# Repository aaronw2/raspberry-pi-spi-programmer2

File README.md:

SOIC-8 and SOIC-16 SPI Flash Programming Hat for Raspberry PI

This hat allows the Raspberry PI to program both SOIC-8 and SOIC-16 SPI
NOR devices at 1.8 and 3.3 volts.  All features of this programmer can
be controlled via software.

While the current version of the board has switches and jumpers present,
a future version of this board will no longer require them since everything
can be controlled by GPIO pins.

SW1: This switch will enable and disable the programmer.  When disabled,
the power and signals to the sockets will be disabled and SPI NOR chips
may be safely installed or removed.  Software is able to read this switch
and a future software version will be able to override the switch.

SW2: This sets the voltage to use for powering and programming the SPI NOR
chips.  Software can read the position of this switch and a future version
of the software will be able to both read and override the switch setting.

JP1: This jumper should be installed if the board this hat is plugged into
does not support SPI chip select 1.  For example, the Rock64Pro board does
not provide CS1.  Software can read whether this jumper is installed or not
and can override the jumper.  A future version of the software will not
need the jumper since it will detect what type of board it is running on.

The SOIC-16 socket will only run in single lane mode.  Lanes 1, 2 and 3
are not supported by the Raspberry PI.

LEDs:
This board has 6 LEDs.

Power: D6: The white LED in the upper left will be lit when 5V is present.
Enabled: D1: This red LED will be lit when power is enabled to the sockets.
3.3V: D2: This LED will be lit when the board is configured for 3.3V
1.8V: D3: This LED will be lit when the board is configured for 1.8V
CS0: D4: This LED will light when there is activity with SPI CS0.
CS1: D5: This LED will light when there is activity with SPI CS1.

GPIOs used:
BMC17: Pin 13: This pin can be input or output.  If high, then 3.3 volts is
               selected, otherwise 1.8v is selected.  If not driven, then
               switch SW2 will control the signal.
BCM22: Pin 15: This pin is used to disable power and tri-state the outputs
               to the sockets.  This pin can be read, in which case SW1 will
               control the signal, or it may be driven to override the switch.
BCM5: Pin 29:  This pin is used to control whether CS1 is driven by CS0 or not.
               This pin can be read in which case the state can be controlled
               by JP1, or it can be driven to override the jumper.  This is
               needed if the board the hat is plugged in to does not support
               SPI CS1 such as the Rock64Pro board.

SPI pins:
BCM10: Pin 19: SPI MOSI signal
BCM9: Pin 21: SPI MISO signal
BCM11: Pin 23: SPI SCLK
BCM8: Pin 24: SPI CS0
BCM7: Pin 26: SPI CS1

I2C Pins:
BMCM0: Pin 27: EEPROM I2C SDA
BMC1: Pin 28: EEPROM I2C SCL

Power: This board draws power from 5V and 3.3V for internal logic.  The
       sockets power and socket I/O is controlled by a built-in regulator
       that uses the 5V supply to generate either 1.8 or 3.3V.

All parts can be found at https://digikey.com

=========== Using ==============

Do not install SPI NOR flash devices in both sockets at the same time.  A
future version of this board may support devices in both sockets.

1. Make sure that the board is in the disabled state
2. Select the proper voltage for the devices
3. Install a SOIC-8 and/or SOIC-16 SPI NOR device into the appropriate socket.
   Note: If not using a Raspberry PI do not install devices in both
         sockets.
4. Run the software to program the device(s)
5. Wait until programming is finished and make sure the enabled LED is not
   lit.  Set the switch to the disabled position.
6. Remove the SPI device

Software: TBD
Todo: Get the board back and assemble and test it then work on software.

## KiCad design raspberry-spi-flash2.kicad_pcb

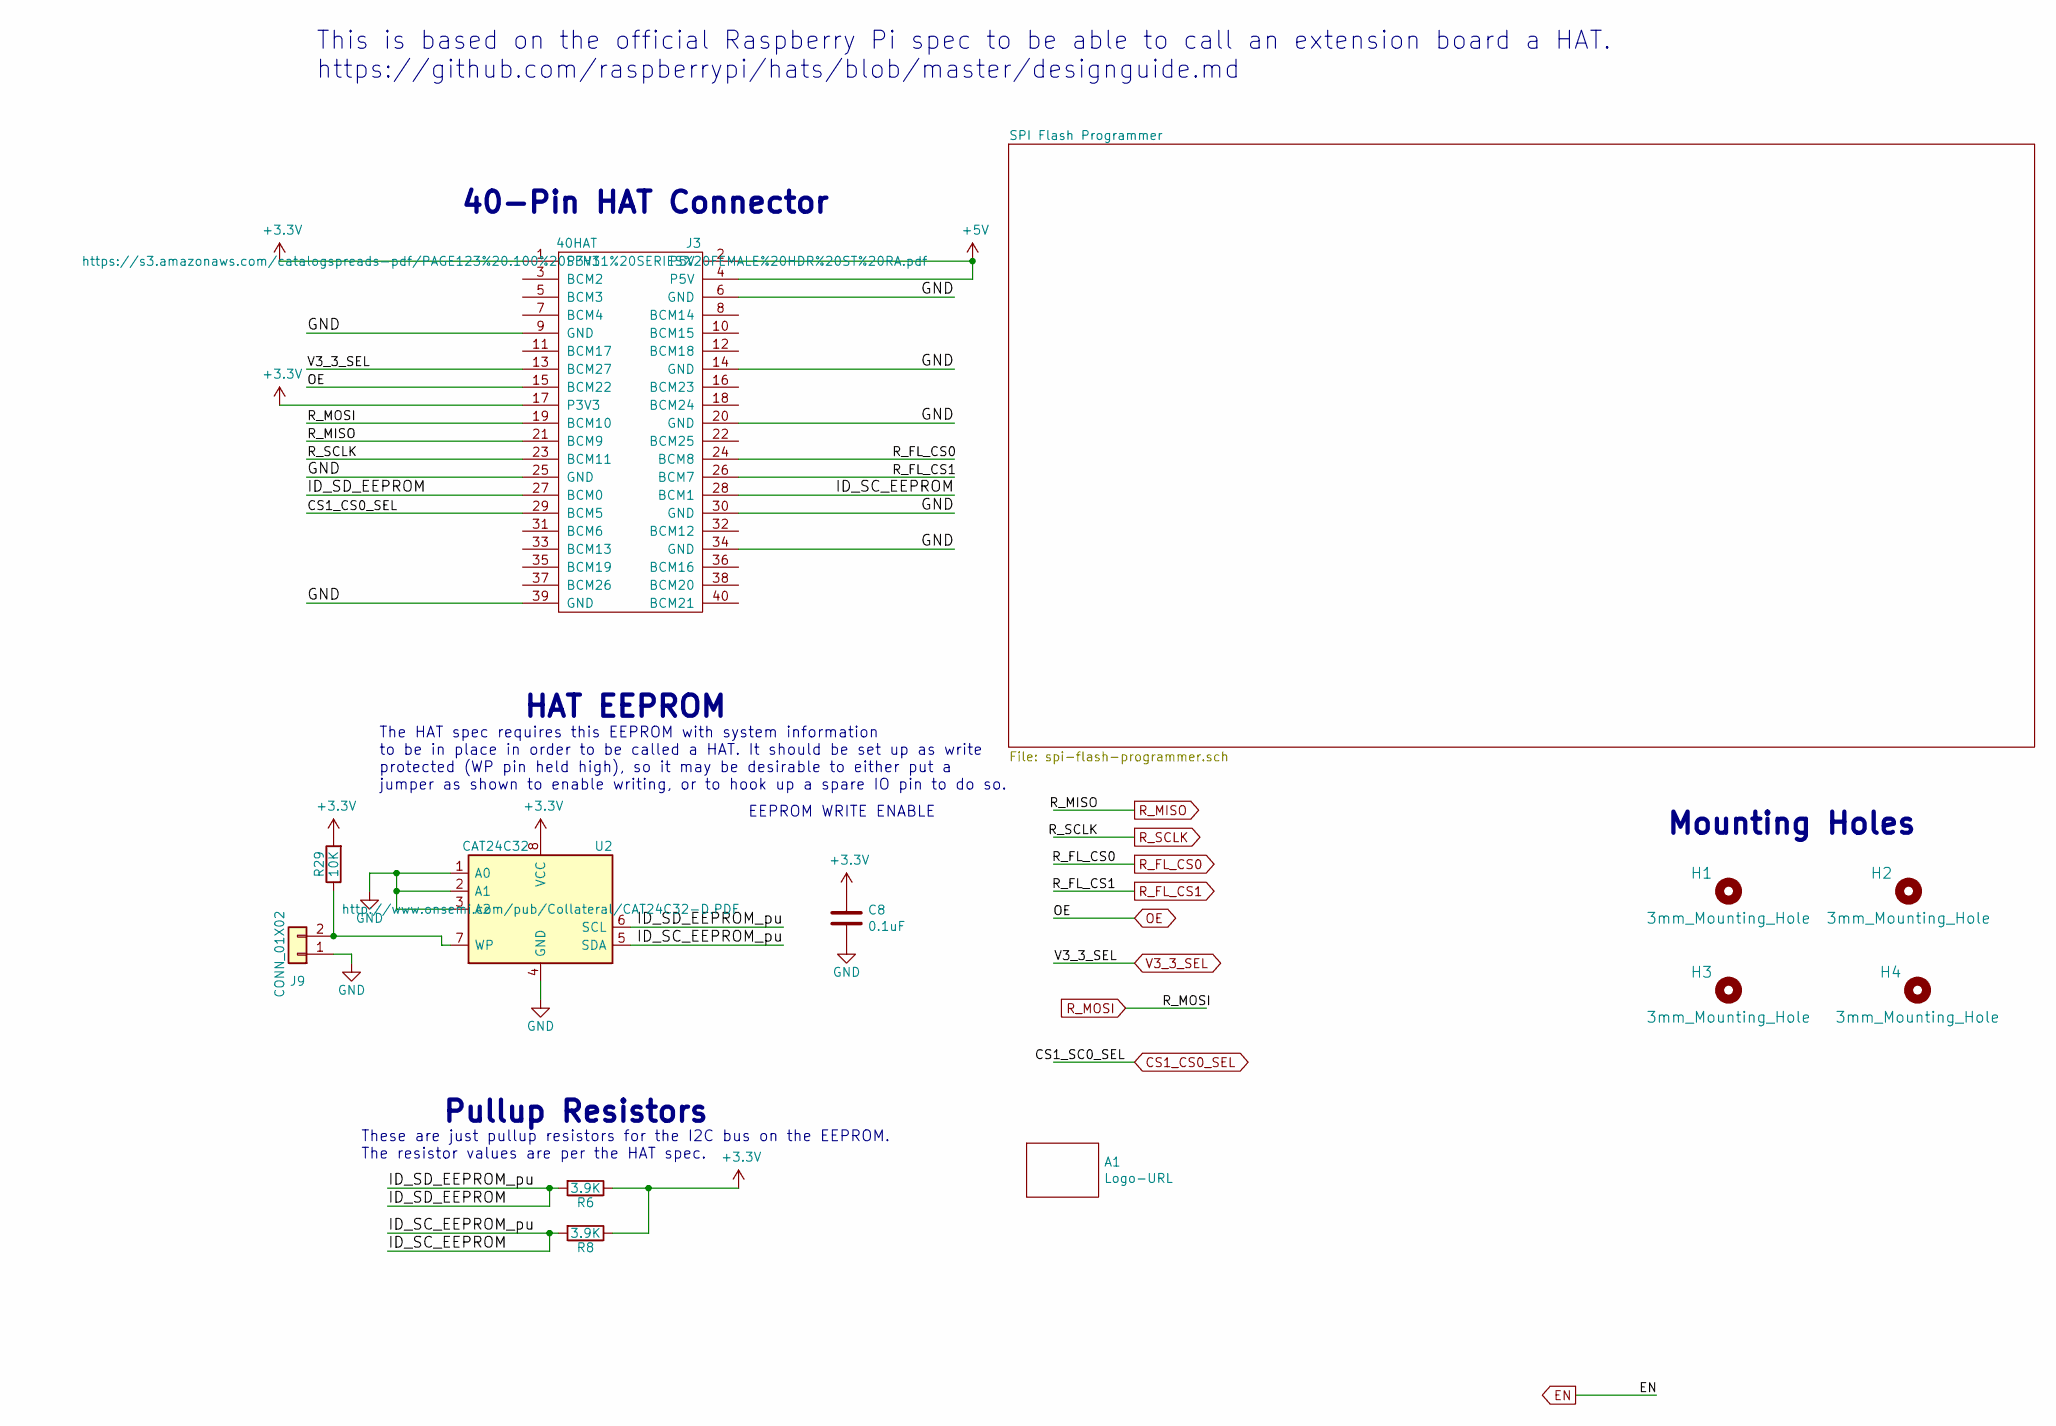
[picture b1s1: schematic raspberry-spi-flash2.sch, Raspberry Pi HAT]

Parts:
A1: Logo-URL; LOGO-raspberry-pi-spi-programmer2
C8: 0.1uF; C_0603_1608Metric
H1, H2, H3, H4: 3mm_Mounting_Hole; NPTH_3mm_ID
J3: 40HAT; PinSocket_2x20_P2.54mm_Vertical; MPN SFH11-PBPC-D20-ST-BK
J9: CONN_01X02; PinHeader_1x02_P2.54mm_Vertical
R6: 3.9K; R_0603_1608Metric; MPN RC0603FR-073K9L
R8: 3.9K; R_0603_1608Metric
R29: 10K; R_0603_1608Metric
U2: CAT24C32; SOIC-8_3.9x4.9mm_P1.27mm; MPN CAT24C32WI-GT3

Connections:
+3V3: C8.1, J3.1 (P3V3), J3.17 (P3V3), R6.1, R8.1, R29.2, U2.8 (VCC); also elsewhere on the board
+5V: J3.2 (P5V), J3.4 (P5V); also elsewhere on the board
/ID_SC_EEPROM: J3.28 (BCM1), R8.2, U2.5 (SDA)
/ID_SD_EEPROM: J3.27 (BCM0), R6.2, U2.6 (SCL)
CS1_CS0_SEL: J3.29 (BCM5); also elsewhere on the board
GND: C8.2, J3.6 (GND), J3.9 (GND), J3.14 (GND), J3.20 (GND), J3.25 (GND), J3.30 (GND), J3.34 (GND), J3.39 (GND), J9.1, U2.1 (A0), U2.2 (A1), U2.3 (A2), U2.4 (GND); also elsewhere on the board
unnamed: J9.2, R29.1, U2.7 (WP)
OE: J3.15 (BCM22); also elsewhere on the board
R_FL_CS0: J3.24 (BCM8); also elsewhere on the board
R_FL_CS1: J3.26 (BCM7); also elsewhere on the board
R_MISO: J3.21 (BCM9); also elsewhere on the board
R_MOSI: J3.19 (BCM10); also elsewhere on the board
R_SCLK: J3.23 (BCM11); also elsewhere on the board
V3_3_SEL: J3.13 (BCM27); also elsewhere on the board

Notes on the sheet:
EEPROM WRITE ENABLE
Pullup Resistors
HAT EEPROM
Mounting Holes
40-Pin HAT Connector
The HAT spec requires this EEPROM with system information to be in place in order to be called a HAT. It should be set up as write protected (WP pin held high), so it may be desirable to either put a jumper as shown to enable writing, or to hook up a spare IO pin to do so.
These are just pullup resistors for the I2C bus on the EEPROM. The resistor values are per the HAT spec.
This is based on the official Raspberry Pi spec to be able to call an extension board a HAT. https://github.com/raspberrypi/hats/blob/master/designguide.md

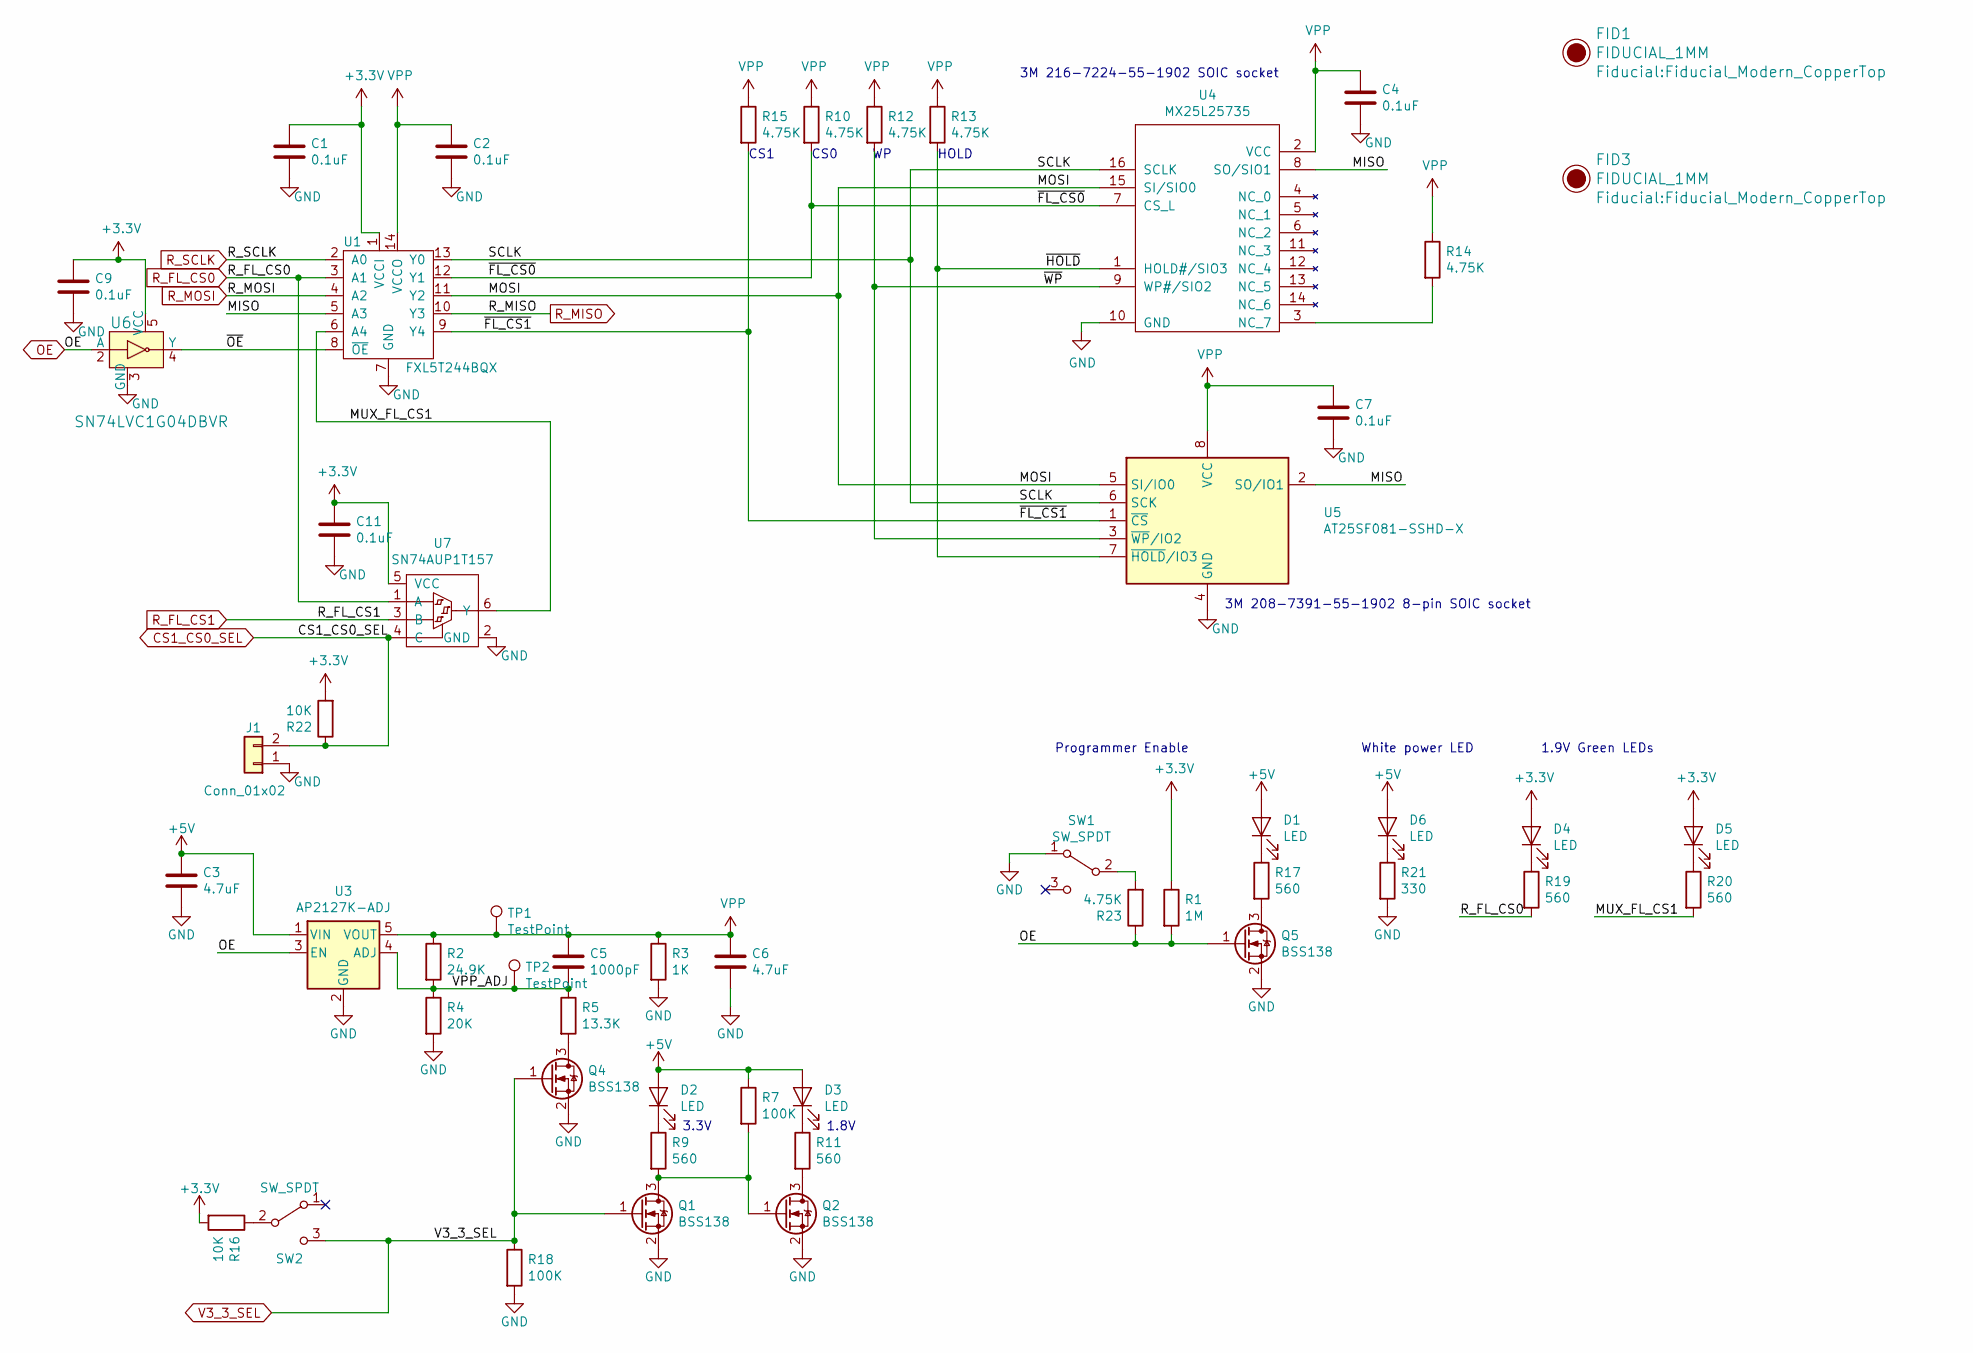
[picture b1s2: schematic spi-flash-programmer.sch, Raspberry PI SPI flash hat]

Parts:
C1, C2, C4, C7, C9, C11: 0.1uF; C_0603_1608Metric
C3, C6: 4.7uF; C_0603_1608Metric
C5: 1000pF; C_0603_1608Metric; MPN GRM188R61E475KE15D
D1, D2, D3: LED; LED_0603_1608Metric
D4, D5, D6: LED; LED_0603_1608Metric; MPN 5990060007F
FID1, FID3: FIDUCIAL_1MM; Fiducial_Modern_CopperTop
J1: Conn_01x02; PinHeader_1x02_P2.54mm_Vertical
Q1, Q2, Q4: BSS138; SOT-23
Q5: BSS138; SOT-23; MPN BSS138K
R1: 1M; R_0603_1608Metric
R2: 24.9K; R_0603_1608Metric; MPN RT0603DRE0724K3L
R3: 1K; R_0603_1608Metric
R4: 20K; R_0603_1608Metric; MPN RT0603FRE0720KL
R5: 13.3K; R_0603_1608Metric; MPN CRCW060313K3FKEA
R7, R18: 100K; R_0603_1608Metric
R9, R11, R17, R19, R20: 560; R_0603_1608Metric
R10, R12, R13, R14, R15, R23: 4.75K; R_0603_1608Metric
R16, R22: 10K; R_0603_1608Metric
R21: 330; R_0603_1608Metric
SW1, SW2: SW_SPDT; SW_STDP_CF-LD-1DC; MPN CF-LD-1DC-AW2W
TP1, TP2: TestPoint; TestPoint_THTPad_1.0x1.0mm_Drill0.5mm
U1: FXL5T244BQX; DQFN-14-1EP_2.5x3mm_EP2.2x1.7mm_Thermal
U3: AP2127K-ADJ; SOT-23-5
U4: MX25L25735; 216-7224-55-1902; MPN 216-7383-55-1902
U5: AT25SF081-SSHD-X; 208-7391-55-1902; MPN 208-7391-55-1902
U6: SN74LVC1G04DBVR; SOT-753; MPN SN74LVC1G04DBVR; Digi-Key_PN 296-11599-1-ND
U7: SN74AUP1T157; SOT-23-6; MPN SN74AUP1T157DCKR

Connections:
+3V3: C1.1, C9.1, C11.1, D4.2 (A), D5.2 (A), R1.1, R16.2, R22.2, U1.1 (VCCI), U6.5 (VCC), U7.5 (VCC); also elsewhere on the board
+5V: C3.1, D1.2 (A), D2.2 (A), D3.2 (A), D6.2 (A), R7.1, U3.1 (VIN); also elsewhere on the board
/SPI Flash Programmer/MISO: U1.5 (A3), U4.8 (SO/SIO1), U5.2 (SO/IO1)
/SPI Flash Programmer/MOSI: U1.11 (Y2), U4.15 (SI/SIO0), U5.5 (SI/IO0)
/SPI Flash Programmer/MUX_FL_CS1: R20.2, U1.6 (A4), U7.6 (Y)
/SPI Flash Programmer/SCLK: U1.13 (Y0), U4.16 (SCLK), U5.6 (SCK)
/SPI Flash Programmer/VPP_ADJ: C5.2, R2.2, R4.1, R5.1, TP2.1, U3.4 (ADJ)
/SPI Flash Programmer/~FL_CS0: R10.2, U1.12 (Y1), U4.7 (CS_L)
/SPI Flash Programmer/~FL_CS1: R15.2, U1.9 (Y4), U5.1 (~CS)
/SPI Flash Programmer/~HOLD: R13.2, U4.1 (HOLD#/SIO3), U5.7 (~HOLD~/IO3)
/SPI Flash Programmer/~OE: U1.8 (~OE), U6.4 (Y)
/SPI Flash Programmer/~WP: R12.2, U4.9 (WP#/SIO2), U5.3 (~WP~/IO2)
CS1_CS0_SEL: J1.2, R22.1, U7.4 (C); also elsewhere on the board
GND: C1.2, C2.2, C3.2, C4.2, C6.2, C7.2, C9.2, C11.2, J1.1, Q1.2 (S), Q2.2 (S), Q4.2 (S), Q5.2 (S), R3.2, R4.2, R18.2, R21.2, SW1.1 (A), U1.7 (GND), U3.2 (GND), U4.10 (GND), U5.4 (GND), U6.3 (GND), U7.2 (GND); also elsewhere on the board
unnamed: D1.1 (K), R17.1
unnamed: D2.1 (K), R9.1
unnamed: D3.1 (K), R11.1
unnamed: D4.1 (K), R19.1
unnamed: D5.1 (K), R20.1
unnamed: D6.1 (K), R21.1
unnamed: Q1.3 (D), Q2.1 (G), R7.2, R9.2
unnamed: Q2.3 (D), R11.2
unnamed: Q4.3 (D), R5.2
unnamed: Q5.3 (D), R17.2
unnamed: R14.2, U4.3 (NC_7)
unnamed: R16.1, SW2.2 (B)
unnamed: R23.2, SW1.2 (B)
OE: Q5.1 (G), R1.2, R23.1, U3.3 (EN), U6.2 (A); also elsewhere on the board
R_FL_CS0: R19.2, U1.3 (A1), U7.1 (A); also elsewhere on the board
R_FL_CS1: U7.3 (B); also elsewhere on the board
R_MISO: U1.10 (Y3); also elsewhere on the board
R_MOSI: U1.4 (A2); also elsewhere on the board
R_SCLK: U1.2 (A0); also elsewhere on the board
V3_3_SEL: Q1.1 (G), Q4.1 (G), R18.1, SW2.3 (C); also elsewhere on the board
VPP: C2.1, C4.1, C5.1, C6.1, C7.1, R2.1, R3.1, R10.1, R12.1, R13.1, R14.1, R15.1, TP1.1, U1.14 (VCCO), U3.5 (VOUT), U4.2 (VCC), U5.8 (VCC)

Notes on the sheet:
1.9V Green LEDs
White power LED
3M 216-7224-55-1902 SOIC socket
3M 208-7391-55-1902 8-pin SOIC socket
3.3V
1.8V
Programmer Enable
CS1
CS0
HOLD

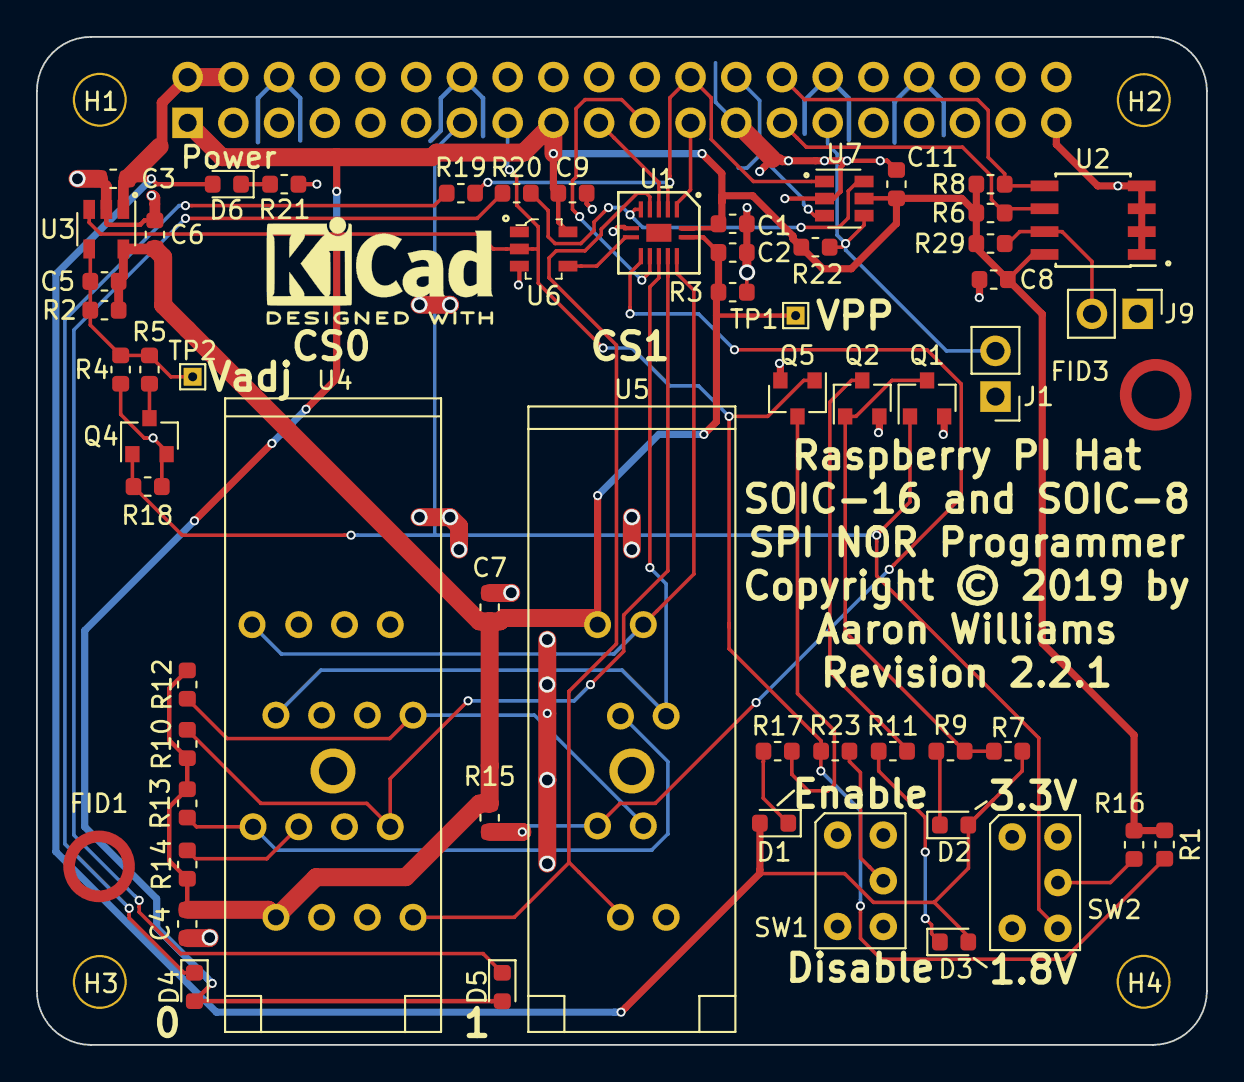
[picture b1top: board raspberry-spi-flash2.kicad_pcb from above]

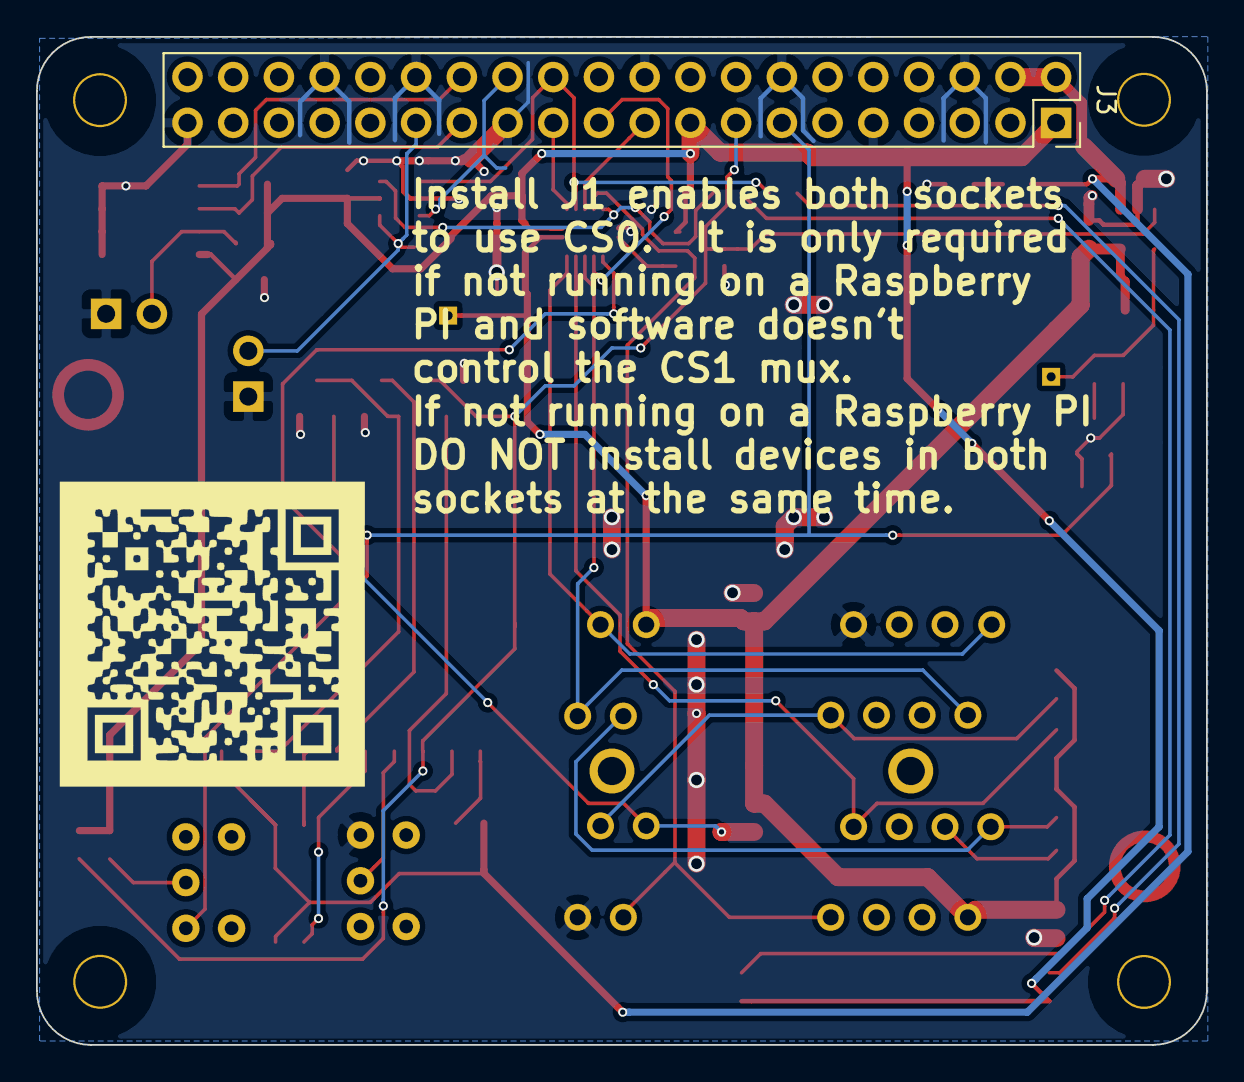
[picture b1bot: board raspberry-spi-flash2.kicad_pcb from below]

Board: 2 copper layers, 65.0 x 56.0 mm, 65 parts (2 on the bottom side), 38 nets.

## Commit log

2019-01-27 Added jumper to work with Rock64 board which lacks CS1.
2019-01-28 Fixes a number of issues
    This fixes a number of issues with the previous design.
    1. The OE GPIO pin was not hooked up.
    2. The level shifter has been changed to a 5 channel unidirectional
    level shifter.
    3. LEDs were moved down near the base.
    4. The switches were fixed based on measuring the contacts with different
2019-01-28 Added missing files.
2019-02-08 Fixed solder mask setting and minor cleanups

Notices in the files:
raspberry-spi-flash2.kicad_pcb:
Copyright © 2019 by
Aaron Williams
spi-flash-programmer.sch:
Copyright (C) 2019 Aaron Williams
